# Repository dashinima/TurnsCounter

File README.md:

# TurnsCounter
Dawu Turns Counter by two Hall effect sensors

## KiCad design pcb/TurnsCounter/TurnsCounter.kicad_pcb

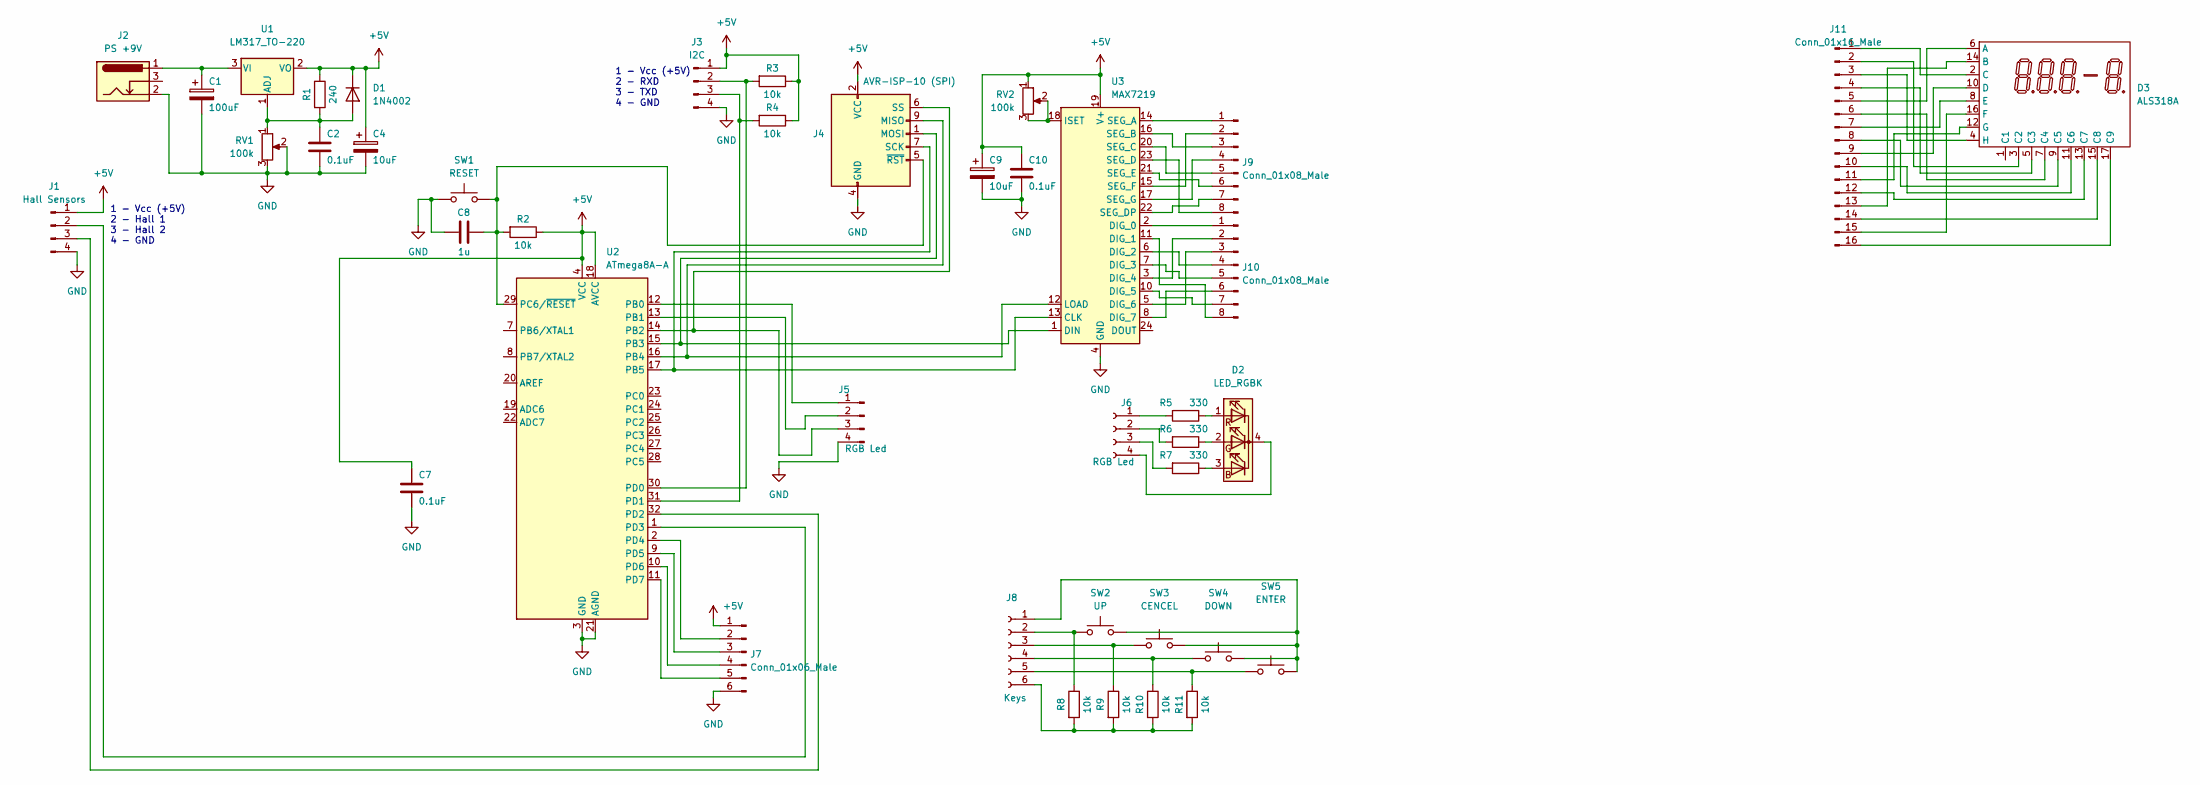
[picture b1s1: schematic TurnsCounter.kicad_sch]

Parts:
C1: 100uF; CP_Radial_D5.0mm_P2.50mm
C2, C7, C10: 0.1uF; C_0805_2012Metric_Pad1.18x1.45mm_HandSolder
C4, C9: 10uF; CP_Radial_D5.0mm_P2.50mm
C8: 1u; C_0805_2012Metric_Pad1.18x1.45mm_HandSolder
D1: 1N4002; D_DO-41_SOD81_P5.08mm_Vertical_KathodeUp
D2: LED_RGBK; LED_D5.0mm-4_RGB_Staggered_Pins
D3: ALS318A
J1: Hall Sensors; PinHeader_1x04_P2.54mm_Vertical
J2: PS +9V; BarrelJack_Horizontal
J3: I2C; PinHeader_1x04_P2.54mm_Vertical
J4: AVR-ISP-10 (SPI); IDC-Header_2x05_P2.54mm_Vertical
J5, J6: RGB Led; PinSocket_1x04_P2.54mm_Vertical
J7: Conn_01x06_Male; PinSocket_1x06_P2.54mm_Vertical
J8: Keys; PinSocket_1x06_P2.54mm_Vertical
J9, J10: Conn_01x08_Male; PinSocket_1x08_P2.54mm_Vertical
J11: Conn_01x16_Male; PinSocket_1x16_P2.54mm_Vertical
R1: 240; R_0805_2012Metric_Pad1.20x1.40mm_HandSolder
R2, R3, R4, R8, R9, R10, R11: 10k; R_0805_2012Metric_Pad1.20x1.40mm_HandSolder
R5, R6, R7: 330; R_0805_2012Metric_Pad1.20x1.40mm_HandSolder
RV1, RV2: 100k; Potentiometer_Bourns_3266W_Vertical
SW1: RESET; SW_PUSH_6mm_2
SW2: UP; SW_PUSH_6mm_2
SW3: CENCEL; SW_PUSH_6mm_2
SW4: DOWN; SW_PUSH_6mm_2
SW5: ENTER; SW_PUSH_6mm_2
U1: LM317_TO-220; TO-220-3_Vertical
U2: ATmega8A-A; TQFP-32_7x7mm_P0.8mm
U3: MAX7219; SOIC-24W_7.5x15.4mm_P1.27mm

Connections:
+5V: C4.1, C7.1, C9.1, C10.1, D1.1 (K), J1.1, J3.1, J4.2 (VCC), J7.1, R1.1, R2.1, R3.1, R4.1, RV2.1, U1.2 (VO), U2.4 (VCC), U2.6 (VCC), U2.18 (AVCC), U3.19 (V+)
GND: C1.2, C2.2, C4.2, C7.2, C8.1, C9.2, C10.2, J1.4, J2.2, J3.4, J4.4 (GND), J4.8 (GND), J4.10 (GND), J5.4, J7.6, RV1.2, RV1.3, SW1.1, U2.3 (GND), U2.5 (GND), U2.21 (AGND), U3.4 (GND), U3.9 (GND)
unnamed: C1.1, J2.1, U1.3 (VI)
unnamed: C2.1, D1.2 (A), R1.2, RV1.1, U1.1 (ADJ)
unnamed: C8.2, J4.5 (~RST), R2.2, SW1.2, U2.29 (PC6/~RESET)
unnamed: D2.1 (RA), R5.1
unnamed: D2.2 (GA), R6.1
unnamed: D2.3 (BA), R7.1
unnamed: D2.4 (K), J6.4
unnamed: D3.2 (C), J11.1
unnamed: D3.3 (C2), J11.2
unnamed: D3.4 (H), J11.3
unnamed: D3.5 (C3), J11.4
unnamed: D3.6 (A), J11.5
unnamed: D3.7 (C4), J11.6
unnamed: D3.8 (E), J11.7
unnamed: D3.9 (C5), J11.8
unnamed: D3.10 (D), J11.9
unnamed: D3.11 (C6), J11.10
unnamed: D3.12 (G), J11.11
unnamed: D3.13 (C7), J11.12
unnamed: D3.14 (B), J11.13
unnamed: D3.15 (C8), J11.14
unnamed: D3.16 (F), J11.15
unnamed: D3.17 (C9), J11.16
unnamed: J1.2, U2.1 (PD3)
unnamed: J1.3, U2.32 (PD2)
unnamed: J3.2, R3.2, U2.30 (PD0)
unnamed: J3.3, R4.2, U2.31 (PD1)
unnamed: J4.1 (MOSI), U2.15 (PB3), U3.1 (DIN)
unnamed: J4.6 (SS), J5.3, U2.14 (PB2)
unnamed: J4.7 (SCK), U2.17 (PB5), U3.13 (CLK)
unnamed: J4.9 (MISO), U2.16 (PB4), U3.12 (LOAD)
unnamed: J5.1, U2.12 (PB0)
unnamed: J5.2, U2.13 (PB1)
unnamed: J6.1, R5.2
unnamed: J6.2, R6.2
unnamed: J6.3, R7.2
unnamed: J7.2, U2.2 (PD4)
unnamed: J7.3, U2.9 (PD5)
unnamed: J7.4, U2.10 (PD6)
unnamed: J7.5, U2.11 (PD7)
unnamed: J8.1, SW2.2, SW3.2, SW4.2, SW5.2
unnamed: J8.2, R8.1, SW2.1
unnamed: J8.3, R9.1, SW3.1
unnamed: J8.4, R10.1, SW4.1
unnamed: J8.5, R11.1, SW5.1
unnamed: J8.6, R8.2, R9.2, R10.2, R11.2
unnamed: J9.1, U3.14 (SEG_A)
unnamed: J9.2, U3.15 (SEG_F)
unnamed: J9.3, U3.16 (SEG_B)
unnamed: J9.4, U3.17 (SEG_G)
unnamed: J9.5, U3.20 (SEG_C)
unnamed: J9.6, U3.21 (SEG_E)
unnamed: J9.7, U3.22 (SEG_DP)
unnamed: J9.8, U3.23 (SEG_D)
unnamed: J10.1, U3.2 (DIG_0)
unnamed: J10.2, U3.3 (DIG_4)
unnamed: J10.3, U3.5 (DIG_6)
unnamed: J10.4, U3.6 (DIG_2)
unnamed: J10.5, U3.7 (DIG_3)
unnamed: J10.6, U3.8 (DIG_7)
unnamed: J10.7, U3.10 (DIG_5)
unnamed: J10.8, U3.11 (DIG_1)
unnamed: RV2.2, RV2.3, U3.18 (ISET)

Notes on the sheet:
1 - Vcc (+5V) 2 - RXD 3 - TXD 4 - GND
1 - Vcc (+5V) 2 - Hall 1 3 - Hall 2 4 - GND

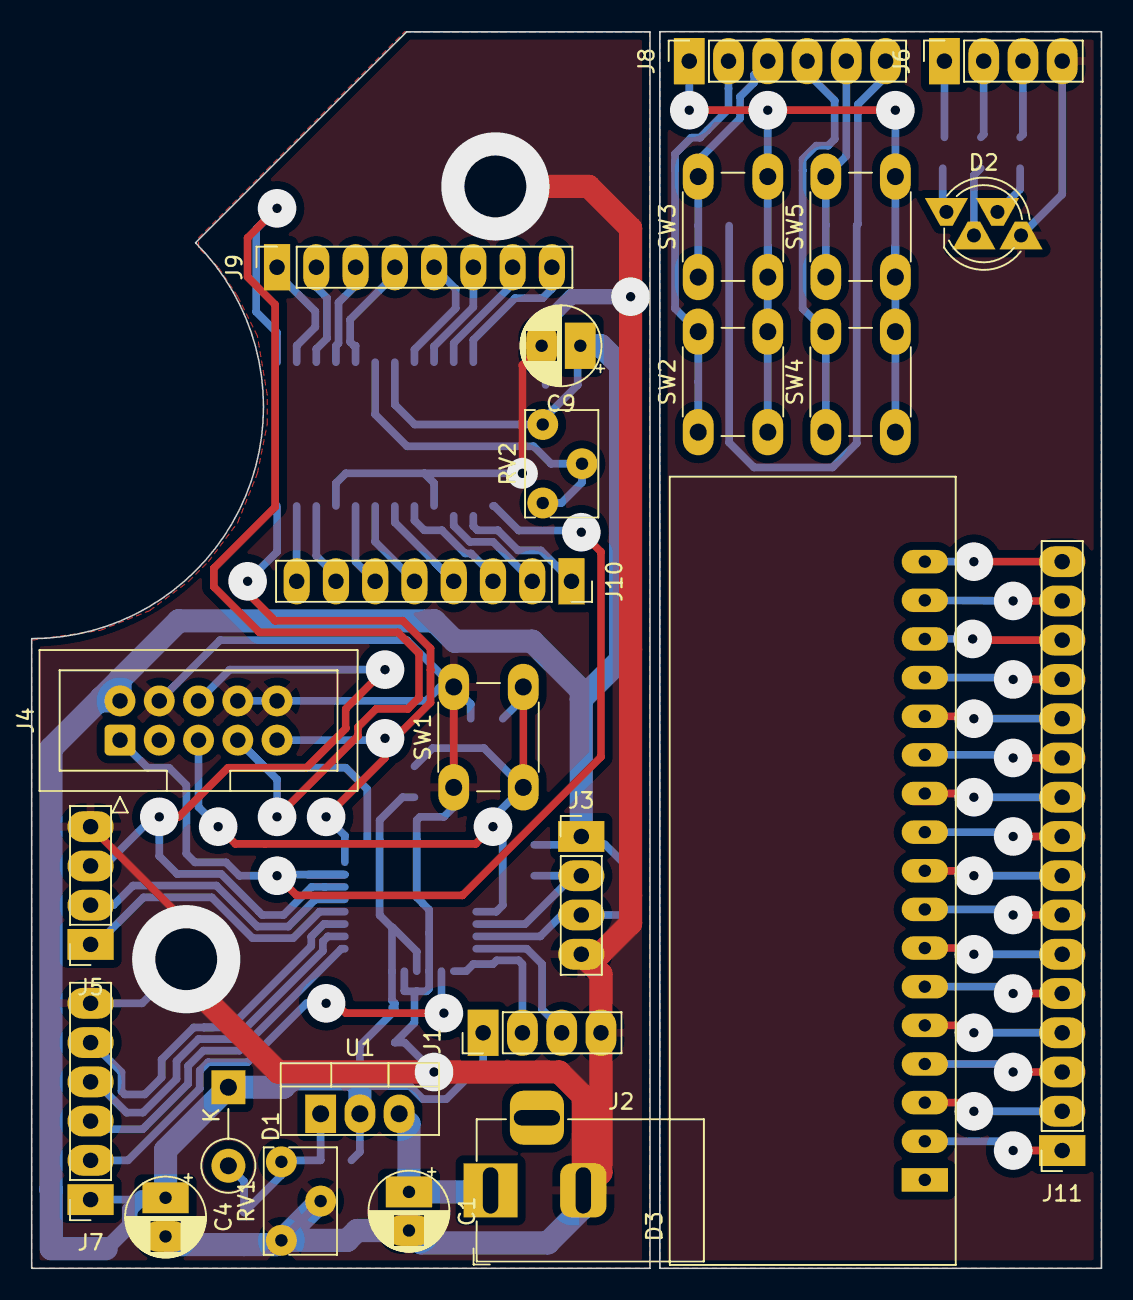
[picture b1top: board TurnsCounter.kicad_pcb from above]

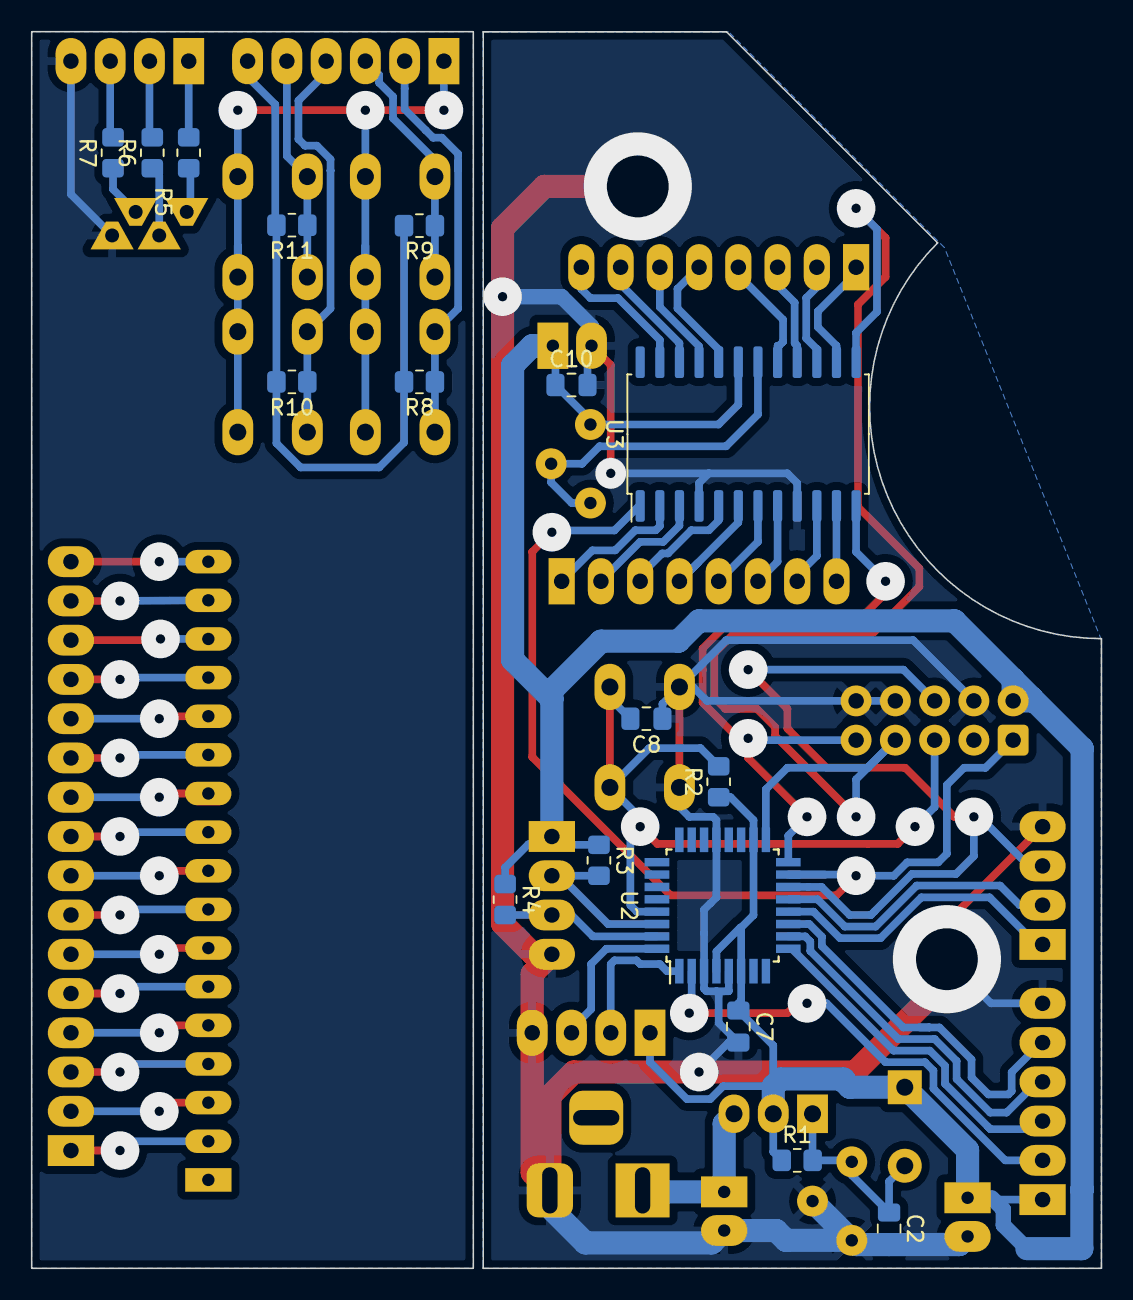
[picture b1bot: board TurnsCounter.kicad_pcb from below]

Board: 2 copper layers, 69.2 x 80.0 mm, 42 parts (17 on the bottom side), 65 nets.

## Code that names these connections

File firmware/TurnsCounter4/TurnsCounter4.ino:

#include <Wire.h> 
#include "DigitLedDisplay.h"
#include <EEPROM.h>


//  Arduino Pin to Display Pin
//   7 to DIN,      PB3 - 15 pin (11)
//   6 to CS,       PB4 - 16 pin (12)
//   5 to CLK     PB5 - 17 pin (13)
DigitLedDisplay ld = DigitLedDisplay(PIN_PB3, PIN_PB4, PIN_PB5);

// Configuration

int pinHallSensor1 = PIN_PD2; // D2          <------- First Hall Sensor
int Interrupt_H1 = 0;   // D2 - INT 0
int pinHallSensor2 = PIN_PD3; // D3          <------- Second Hall Sensor
int Interrupt_H2 = 1;   // D3 - INT 1


byte LED_PIN_G = PIN_PB0; // 8
byte LED_PIN_B = PIN_PB1; // 9;
byte LED_PIN_R = PIN_PB2; // 10;

//test

volatile int addr = 0;
struct LastDataType {
  byte CurrentIndex = 0;
  volatile long TurnsCountArray[10] = {0, 0, 0, 0, 0, 0, 0, 0, 0, 0};
};
volatile LastDataType LastData;

// Other Vars
volatile boolean Hall_1_IsRising = false;
volatile boolean Hall_2_IsRising = false;
volatile unsigned long Hall_1_mills = 0;
volatile unsigned long Hall_2_mills = 0;

volatile boolean IsNextTurn = false;
volatile long TurnsCount = 0;

//################################################################
//################################################################
//################################################################
void setup()
{
  /* Set the brightness min:1, max:15 */
  ld.setBright(10);

  /* Set the digit count */
  ld.setDigitLimit(8);
  
    
  pinMode(LED_PIN_R, OUTPUT);
  digitalWrite(LED_PIN_R, HIGH);
  pinMode(LED_PIN_G, OUTPUT);
  digitalWrite(LED_PIN_G, HIGH);
  pinMode(LED_PIN_B, OUTPUT);
  digitalWrite(LED_PIN_B, HIGH);

  pinMode(pinHallSensor1, INPUT);
  pinMode(pinHallSensor2, INPUT);
  attachInterrupt(Interrupt_H1, HallSensor_1, RISING);
  attachInterrupt(Interrupt_H2, HallSensor_2, RISING);

//  //Writing Zero Data to EEPROM
//  TurnsCount = 0;
//  for (byte i = 1; i <= 10; i++) {
//    LastData.CurrentIndex = i;
//    LastData.TurnsCountArray[ LastData.CurrentIndex ] = LastData.CurrentIndex;
//  }
//  EEPROM.put(addr, LastData);   
//  digitalWrite(LED_PIN_G, LOW);
  
  // Restore Last Data from EEPROM, Read and Display Typing
  EEPROM.get( addr, LastData);
  byte thisIndex = 0;
  for (byte i = 1; i <= 10; i++) {
    if ( (LastData.CurrentIndex+i)<=10 ) {
      thisIndex = i;
    }
    else {
      thisIndex = (LastData.CurrentIndex+i)-10;
    };
    TurnsCount = LastData.TurnsCountArray[ thisIndex ];
    ld.printDigit(TurnsCount);
    delay(1500);
  };
  
  TurnsCount = 0;
  IsNextTurn = true;
}

//################################################################
//################################################################
//################################################################
ISR(RESET_vect) {
  // ----------------
  LastData.CurrentIndex = LastData.CurrentIndex+1;
  if (LastData.CurrentIndex>10) {
    LastData.CurrentIndex = 1;
  };
  LastData.TurnsCountArray[ LastData.CurrentIndex+1 ] = TurnsCount;
  EEPROM.put(addr, LastData);
}
void HallSensor_1() {
  Hall_1_IsRising = true;  
  Hall_1_mills = micros();
}
void HallSensor_2() {
  Hall_2_IsRising = true;  
  Hall_2_mills = micros();
}

//################################################################
//################################################################
//################################################################
void loop()
{
  //*********************************************
  
  if ( (Hall_1_IsRising == true) && (Hall_2_IsRising == true) ) { 
    if ( Hall_1_mills < Hall_2_mills ) {                          // Forward count
        TurnsCount = TurnsCount + 1;
    }
    if (Hall_1_mills > Hall_2_mills) {                            // Revers count
        TurnsCount = TurnsCount - 1;
    }
        Hall_1_IsRising = false;
        Hall_2_IsRising = false;
  }
  //*********************************************
  
  //*********************************************
  ld.printDigit(TurnsCount);
}

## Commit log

2022-08-05 add files
2022-08-05 add some models
2022-08-05 test
2022-08-05 git cmd
2022-08-05 pcb alpha, xtal deleted
2022-08-06 archives
2022-08-06 First PCB
2022-08-08 New PCB with copper area
2022-08-09 Pcb...
2022-08-24 pcb fin
2022-08-24 pcb fin flatcam project
2022-08-30 Add some Arduino sketches for testing hardware peripheries.
2022-08-30 FW v.4
2022-09-16 2022-09-16
